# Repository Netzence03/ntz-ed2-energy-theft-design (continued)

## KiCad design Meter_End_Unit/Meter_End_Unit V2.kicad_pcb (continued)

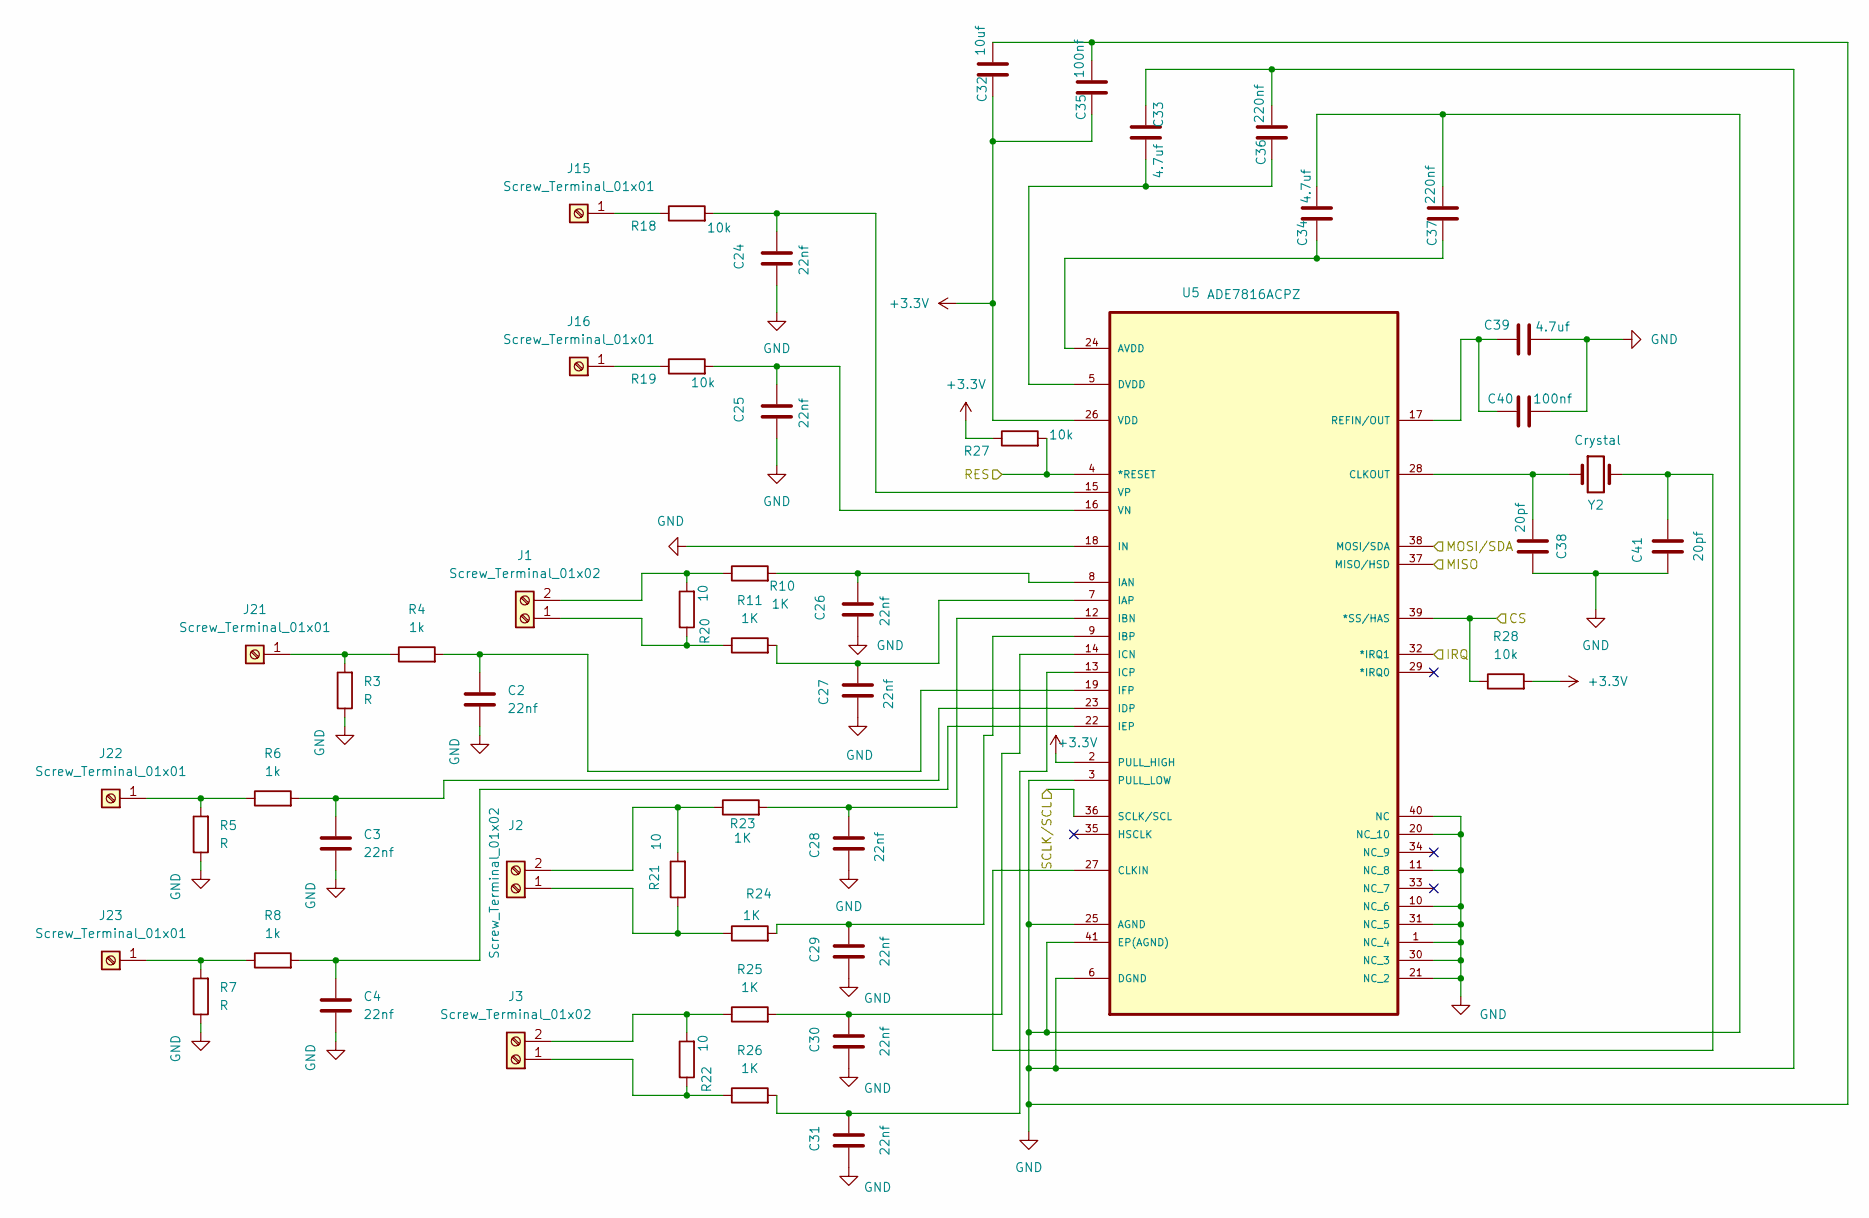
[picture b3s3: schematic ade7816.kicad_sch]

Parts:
C2, C3, C4, C24, C25, C26, C27, C28, C29, C30, C31: 22nf; C_0805_2012Metric
C32: 10uf; C_0805_2012Metric
C33, C34, C39: 4.7uf; C_0805_2012Metric
C35, C40: 100nf; C_0805_2012Metric
C36, C37: 220nf; C_0805_2012Metric
C38, C41: 20pf; C_0805_2012Metric
J1, J2, J3: Screw_Terminal_01x02; TerminalBlock_Phoenix_PTSM-0,5-2-2,5-V-SMD_1x02-1MP_P2.50mm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
J15, J16, J21, J22, J23: Screw_Terminal_01x01; TerminalBlock_1x01_P5.08mm
R3, R5, R7: R; R_0805_2012Metric
R4, R6, R8: 1k; R_0805_2012Metric
R10, R11, R23, R24, R25, R26: 1K; R_0805_2012Metric
R18, R19, R27, R28: 10k; R_0805_2012Metric
R20, R21, R22: 10; R_0805_2012Metric
U5: ADE7816ACPZ; QFN50P600X600X80-41N; MPN ADE7816ACPZ
Y2: Crystal; Crystal_SMD_3225-4Pin_3.2x2.5mm

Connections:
+3.3V: C32.1, C35.1, R27.1, R28.2, U5.2 (PULL_HIGH), U5.26 (VDD); also elsewhere on the board
/ESP32/CS: R28.1, U5.39 (*SS/HAS); also elsewhere on the board
/ESP32/IRQ: U5.32 (*IRQ1); also elsewhere on the board
/ESP32/MISO: U5.37 (MISO/HSD); also elsewhere on the board
/ESP32/MOSI/SDA: U5.36 (SCLK/SCL); also elsewhere on the board
/ESP32/RES: R27.2, U5.4 (*RESET); also elsewhere on the board
/ESP32/SCLK/SCL: U5.38 (MOSI/SDA); also elsewhere on the board
GND: C2.2, C3.2, C4.2, C24.1, C25.1, C26.1, C27.1, C28.1, C29.1, C30.1, C31.1, C32.2, C33.1, C34.2, C35.2, C36.2, C37.2, C38.1, C39.2, C40.2, C41.1, R3.1, R5.1, R7.1, U5.1 (NC_4), U5.3 (PULL_LOW), U5.6 (DGND), U5.10 (NC_6), U5.11 (NC_8), U5.18 (IN), U5.20 (NC_10), U5.21 (NC_2), U5.25 (AGND), U5.30 (NC_3), U5.31 (NC_5), U5.40 (NC), U5.41 (EP(AGND)); also elsewhere on the board
unnamed: J1.1, R11.1, R20.1
unnamed: J1.2, R10.1, R20.2
unnamed: J2.1, R21.1, R24.1
unnamed: J2.2, R21.2, R23.1
unnamed: J3.1, R22.1, R26.1
unnamed: J3.2, R22.2, R25.1
unnamed: J15.1, R18.1
unnamed: J16.1, R19.1
unnamed: J21.1, R3.2, R4.1
unnamed: J22.1, R5.2, R6.1
unnamed: J23.1, R7.2, R8.1
unnamed: C34.1, C37.1, U5.24 (AVDD)
unnamed: C41.2, U5.27 (CLKIN), Y2.2
unnamed: C38.2, U5.28 (CLKOUT), Y2.1
unnamed: C33.2, C36.1, U5.5 (DVDD)
unnamed: C26.2, R10.2, U5.8 (IAN)
unnamed: C27.2, R11.2, U5.7 (IAP)
unnamed: C28.2, R23.2, U5.12 (IBN)
unnamed: C29.2, R24.2, U5.9 (IBP)
unnamed: C30.2, R25.2, U5.14 (ICN)
unnamed: C31.2, R26.2, U5.13 (ICP)
unnamed: C3.1, R6.2, U5.23 (IDP)
unnamed: C4.1, R8.2, U5.22 (IEP)
unnamed: C2.1, R4.2, U5.19 (IFP)
unnamed: C39.1, C40.1, U5.17 (REFIN/OUT)
unnamed: C25.2, R19.2, U5.16 (VN)
unnamed: C24.2, R18.2, U5.15 (VP)

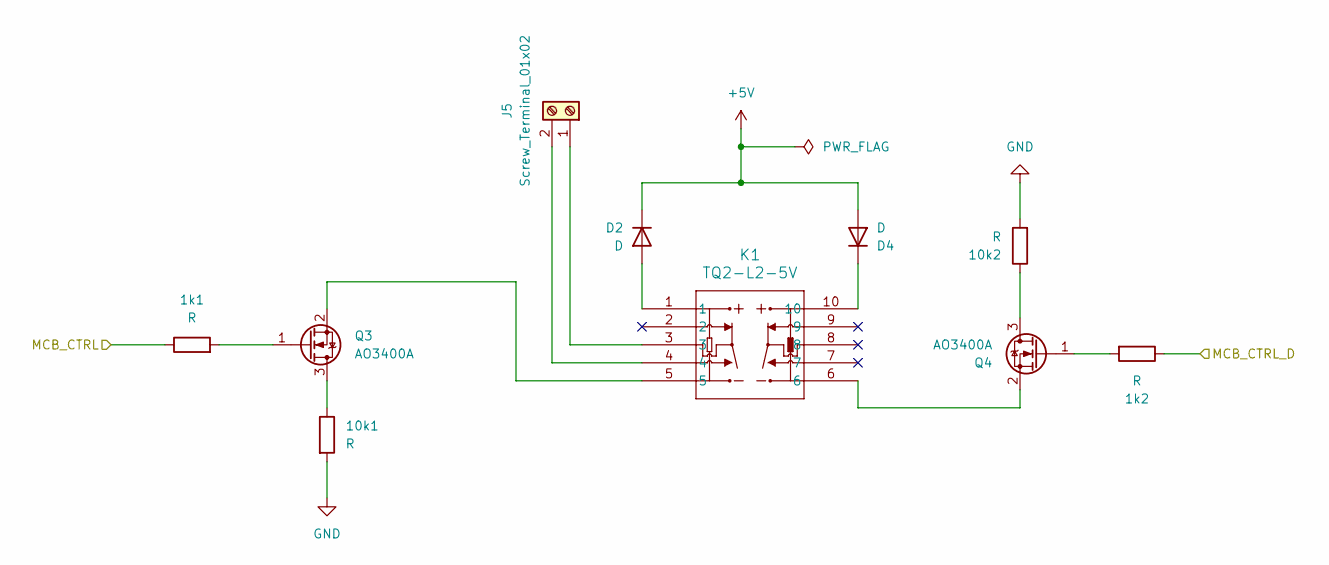
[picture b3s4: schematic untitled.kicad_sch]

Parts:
1k1, 1k2, 10k1, 10k2: R; R_0805_2012Metric
D2, D4: D; D_SOD-123
J5: Screw_Terminal_01x02; TerminalBlock_Phoenix_PTSM-0,5-2-2,5-V-SMD_1x02-1MP_P2.50mm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
K1: TQ2-L2-5V; RELAY_TQ2_2C_PAN
Q3, Q4: AO3400A; SOT-23

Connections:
+5V: D2.1 (K), D4.2 (A); also elsewhere on the board
/ESP32/MCB_CTRL: 1k1.1; also elsewhere on the board
/ESP32/MCB_CTRL_D: 1k2.1; also elsewhere on the board
GND: 10k1.2, 10k2.2; also elsewhere on the board
unnamed: D2.2 (A), K1.1
unnamed: D4.1 (K), K1.10
unnamed: J5.1, K1.3
unnamed: J5.2, K1.4
unnamed: 10k1.1, Q3.3 (D)
unnamed: 1k1.2, Q3.1 (G)
unnamed: K1.5, Q3.2 (S)
unnamed: 10k2.1, Q4.3 (D)
unnamed: 1k2.2, Q4.1 (G)
unnamed: K1.6, Q4.2 (S)

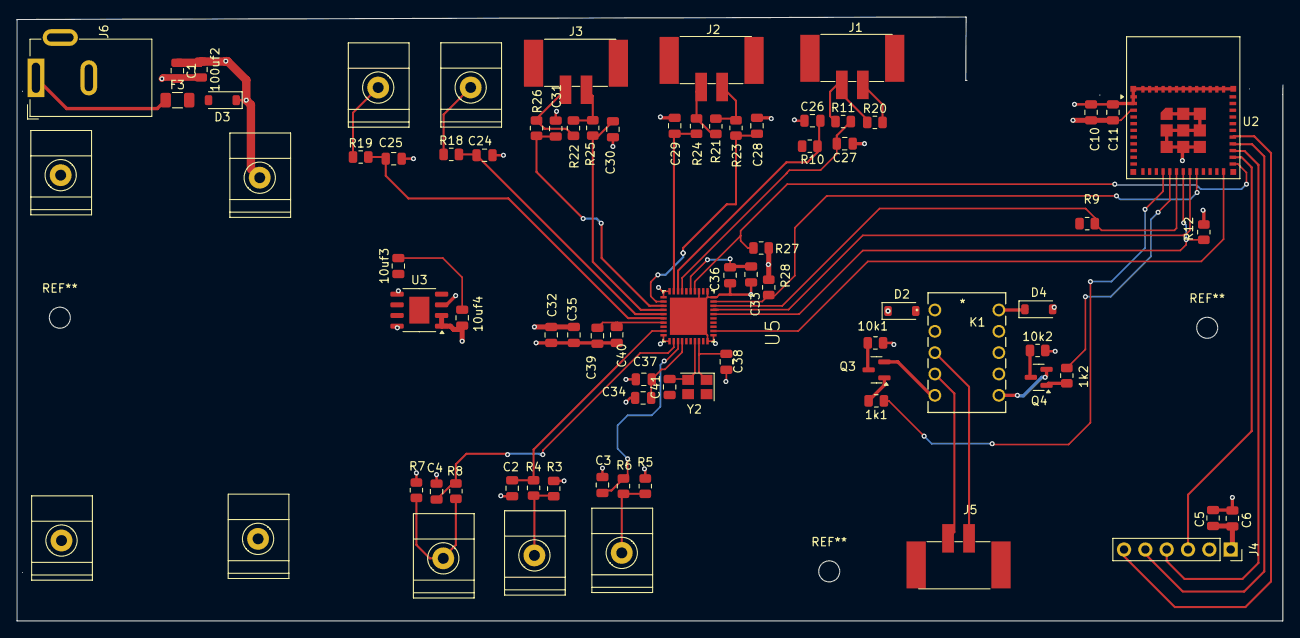
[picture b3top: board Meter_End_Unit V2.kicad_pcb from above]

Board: 4 copper layers, 150.7 x 71.9 mm, 80 parts (0 on the bottom side), 56 nets.

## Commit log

2026-02-02 Initial schematic and PCB design
2026-02-02 Change schematic and PCB design
2026-02-02 Change in the Pole End Unit
2026-02-02 Update in footprint
2026-02-12 PCB design for meter
2026-02-20 Production design
2026-02-27 Chnages in power and ADE7816
2026-03-09 PCB Design
2026-03-16 BOM List
2026-03-16 Updated BOM List
2026-03-17 update in BOM list
